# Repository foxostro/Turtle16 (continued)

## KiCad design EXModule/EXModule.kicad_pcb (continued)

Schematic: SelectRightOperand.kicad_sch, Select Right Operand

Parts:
C3, C4, C5, C6, C7: 100nF; C_0603_1608Metric_Pad1.08x0.95mm_HandSolder
U2, U3, U5, U6: 74AHCT16245; TSSOP-48_6.1x12.5mm_P0.5mm
U4: 74AHCT138; TSSOP-16_4.4x5mm_P0.65mm

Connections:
/EX Prototype Inputs/B0: U2.47 (1A1); also elsewhere on the board
/EX Prototype Inputs/B1: U2.46 (1A2); also elsewhere on the board
/EX Prototype Inputs/B2: U2.44 (1A3); also elsewhere on the board
/EX Prototype Inputs/B3: U2.43 (1A4); also elsewhere on the board
/EX Prototype Inputs/B4: U2.41 (1A5); also elsewhere on the board
/EX Prototype Inputs/B5: U2.40 (1A6); also elsewhere on the board
/EX Prototype Inputs/B6: U2.38 (1A7); also elsewhere on the board
/EX Prototype Inputs/B7: U2.37 (1A8); also elsewhere on the board
/EX Prototype Inputs/B8: U2.36 (2A1); also elsewhere on the board
/EX Prototype Inputs/B9: U2.35 (2A2); also elsewhere on the board
/EX Prototype Inputs/B10: U2.33 (2A3); also elsewhere on the board
/EX Prototype Inputs/B11: U2.32 (2A4); also elsewhere on the board
/EX Prototype Inputs/B12: U2.30 (2A5); also elsewhere on the board
/EX Prototype Inputs/B13: U2.29 (2A6); also elsewhere on the board
/EX Prototype Inputs/B14: U2.27 (2A7); also elsewhere on the board
/EX Prototype Inputs/B15: U2.26 (2A8); also elsewhere on the board
/EX Prototype Inputs/Ctl_EX3: U4.1 (A0); also elsewhere on the board
/EX Prototype Inputs/Ctl_EX4: U4.2 (A1); also elsewhere on the board
/EX Prototype Inputs/Ins_EX0: U3.47 (1A1), U5.47 (1A1), U6.47 (1A1); also elsewhere on the board
/EX Prototype Inputs/Ins_EX1: U3.46 (1A2), U5.46 (1A2), U6.46 (1A2); also elsewhere on the board
/EX Prototype Inputs/Ins_EX2: U3.44 (1A3), U6.44 (1A3); also elsewhere on the board
/EX Prototype Inputs/Ins_EX3: U3.43 (1A4), U6.43 (1A4); also elsewhere on the board
/EX Prototype Inputs/Ins_EX4: U3.26 (2A8), U3.27 (2A7), U3.29 (2A6), U3.30 (2A5), U3.32 (2A4), U3.33 (2A3), U3.35 (2A2), U3.36 (2A1), U3.37 (1A8), U3.38 (1A7), U3.40 (1A6), U3.41 (1A5), U6.41 (1A5); also elsewhere on the board
/EX Prototype Inputs/Ins_EX5: U6.40 (1A6); also elsewhere on the board
/EX Prototype Inputs/Ins_EX6: U6.38 (1A7); also elsewhere on the board
/EX Prototype Inputs/Ins_EX7: U6.37 (1A8); also elsewhere on the board
/EX Prototype Inputs/Ins_EX8: U5.44 (1A3), U6.36 (2A1); also elsewhere on the board
/EX Prototype Inputs/Ins_EX9: U5.43 (1A4), U6.35 (2A2); also elsewhere on the board
/EX Prototype Inputs/Ins_EX10: U5.26 (2A8), U5.27 (2A7), U5.29 (2A6), U5.30 (2A5), U5.32 (2A4), U5.33 (2A3), U5.35 (2A2), U5.36 (2A1), U5.37 (1A8), U5.38 (1A7), U5.40 (1A6), U5.41 (1A5), U6.26 (2A8), U6.27 (2A7), U6.29 (2A6), U6.30 (2A5), U6.32 (2A4), U6.33 (2A3); also elsewhere on the board
/EX/ALU/RightOp0: U2.2 (1B1), U3.2 (1B1), U5.2 (1B1), U6.2 (1B1); also elsewhere on the board
/EX/ALU/RightOp1: U2.3 (1B2), U3.3 (1B2), U5.3 (1B2), U6.3 (1B2); also elsewhere on the board
/EX/ALU/RightOp2: U2.5 (1B3), U3.5 (1B3), U5.5 (1B3), U6.5 (1B3); also elsewhere on the board
/EX/ALU/RightOp3: U2.6 (1B4), U3.6 (1B4), U5.6 (1B4), U6.6 (1B4); also elsewhere on the board
/EX/ALU/RightOp4: U2.8 (1B5), U3.8 (1B5), U5.8 (1B5), U6.8 (1B5); also elsewhere on the board
/EX/ALU/RightOp5: U2.9 (1B6), U3.9 (1B6), U5.9 (1B6), U6.9 (1B6); also elsewhere on the board
/EX/ALU/RightOp6: U2.11 (1B7), U3.11 (1B7), U5.11 (1B7), U6.11 (1B7); also elsewhere on the board
/EX/ALU/RightOp7: U2.12 (1B8), U3.12 (1B8), U5.12 (1B8), U6.12 (1B8); also elsewhere on the board
/EX/ALU/RightOp8: U2.13 (2B1), U3.13 (2B1), U5.13 (2B1), U6.13 (2B1); also elsewhere on the board
/EX/ALU/RightOp9: U2.14 (2B2), U3.14 (2B2), U5.14 (2B2), U6.14 (2B2); also elsewhere on the board
/EX/ALU/RightOp10: U2.16 (2B3), U3.16 (2B3), U5.16 (2B3), U6.16 (2B3); also elsewhere on the board
/EX/ALU/RightOp11: U2.17 (2B4), U3.17 (2B4), U5.17 (2B4), U6.17 (2B4); also elsewhere on the board
/EX/ALU/RightOp12: U2.19 (2B5), U3.19 (2B5), U5.19 (2B5), U6.19 (2B5); also elsewhere on the board
/EX/ALU/RightOp13: U2.20 (2B6), U3.20 (2B6), U5.20 (2B6), U6.20 (2B6); also elsewhere on the board
/EX/ALU/RightOp14: U2.22 (2B7), U3.22 (2B7), U5.22 (2B7), U6.22 (2B7); also elsewhere on the board
/EX/ALU/RightOp15: U2.23 (2B8), U3.23 (2B8), U5.23 (2B8), U6.23 (2B8); also elsewhere on the board
GND: C3.2, C4.2, C5.2, C6.2, C7.2, U2.4 (GND), U2.10 (GND), U2.15 (GND), U2.21 (GND), U2.28 (GND), U2.34 (GND), U2.39 (GND), U2.45 (GND), U3.4 (GND), U3.10 (GND), U3.15 (GND), U3.21 (GND), U3.28 (GND), U3.34 (GND), U3.39 (GND), U3.45 (GND), U4.3 (A2), U4.4 (E1), U4.5 (E2), U4.8 (GND), U5.4 (GND), U5.10 (GND), U5.15 (GND), U5.21 (GND), U5.28 (GND), U5.34 (GND), U5.39 (GND), U5.45 (GND), U6.4 (GND), U6.10 (GND), U6.15 (GND), U6.21 (GND), U6.28 (GND), U6.34 (GND), U6.39 (GND), U6.45 (GND); also elsewhere on the board
unnamed: U2.25 (2~OE), U2.48 (1~OE), U4.15 (O0)
unnamed: U3.25 (2~OE), U3.48 (1~OE), U4.14 (O1)
unnamed: U4.12 (O3), U6.25 (2~OE), U6.48 (1~OE)
unnamed: U4.13 (O2), U5.25 (2~OE), U5.48 (1~OE)
VCC: C3.1, C4.1, C5.1, C6.1, C7.1, U2.1 (1DIR), U2.7 (VCC), U2.18 (VCC), U2.24 (2DIR), U2.31 (VCC), U2.42 (VCC), U3.1 (1DIR), U3.7 (VCC), U3.18 (VCC), U3.24 (2DIR), U3.31 (VCC), U3.42 (VCC), U4.6 (E3), U4.16 (VCC), U5.1 (1DIR), U5.7 (VCC), U5.18 (VCC), U5.24 (2DIR), U5.31 (VCC), U5.42 (VCC), U6.1 (1DIR), U6.7 (VCC), U6.18 (VCC), U6.24 (2DIR), U6.31 (VCC), U6.42 (VCC); also elsewhere on the board

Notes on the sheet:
SelRightOp=0 —> Select Register B SelRightOp=1 —> Select Immediate ins[4:0] SelRightOp=2 —> Select Immediate ins[10:8, 1:0] SelRightOp=3 —> Select Immediate ins[10:0]

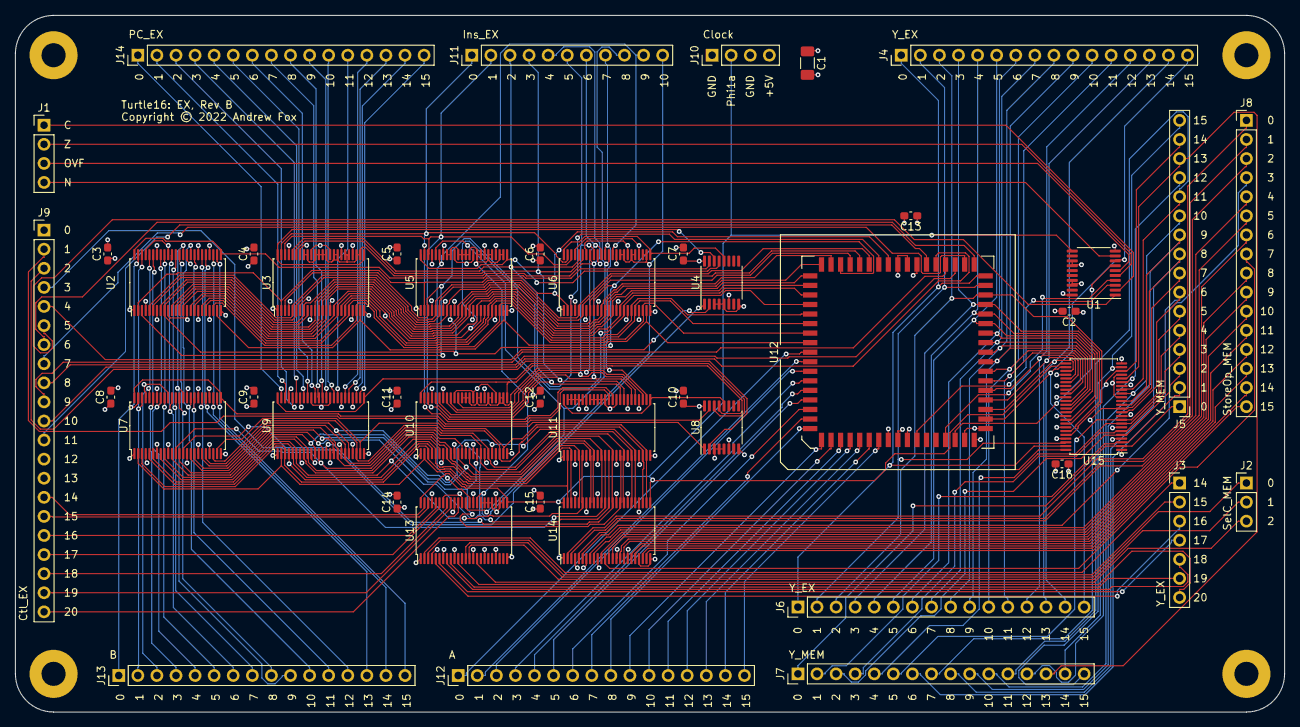
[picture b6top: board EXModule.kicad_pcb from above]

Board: 4 copper layers, 168.9 x 92.7 mm, 49 parts (0 on the bottom side), 185 nets.

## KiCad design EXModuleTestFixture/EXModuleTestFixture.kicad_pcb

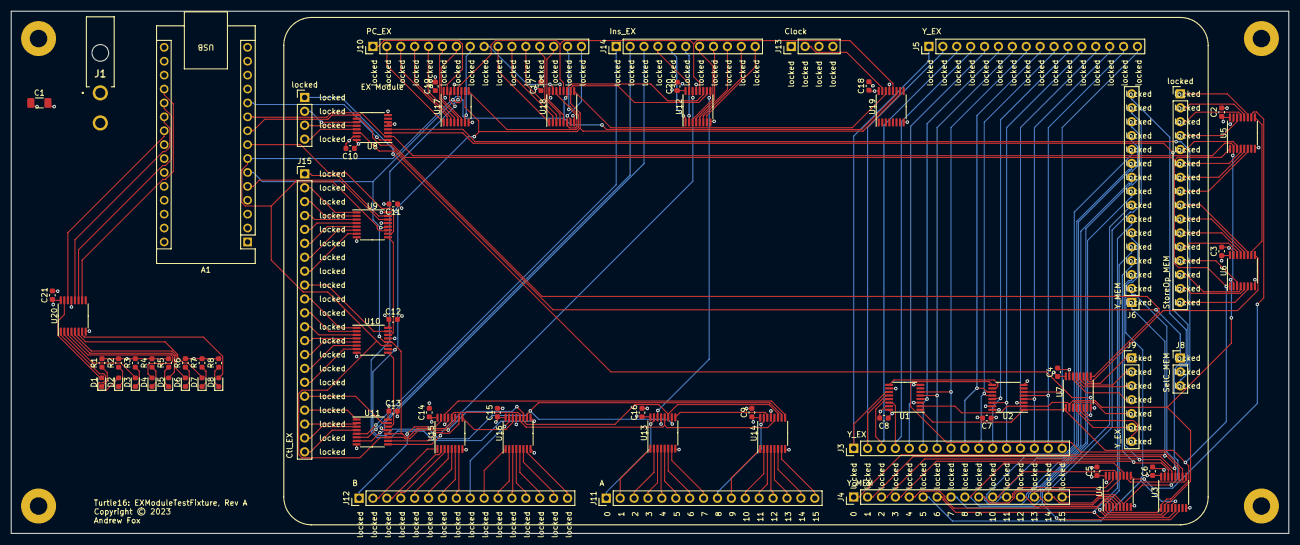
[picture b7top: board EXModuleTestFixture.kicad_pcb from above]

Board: 4 copper layers, 233.4 x 95.4 mm, 77 parts (0 on the bottom side), 189 nets.

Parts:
A1: Arduino_Nano_Every; Arduino_Nano
C1: 100µF; C_1206_3216Metric_Pad1.33x1.80mm_HandSolder
C2, C3, C4, C5, C6, C7, C8, C9, C10, C11, C12, C13, C14, C15, C16, C17, C18, C19, C20, C21: 0.1µF; C_0603_1608Metric
D1, D2, D3, D4, D5, D6, D7, D8: Red; LED_0603_1608Metric
H1, H2, H3, H4: MountingHole_Pad; MountingHole_3.2mm_M3_Pad
J1: Power; 172448-0002
J3, J5: Y_EX; PinHeader_1x16_P2.54mm_Vertical
J4, J6: Y_MEM; PinHeader_1x16_P2.54mm_Vertical
J8: SelC_MEM; PinHeader_1x03_P2.54mm_Vertical
J9: Y_EX; PinHeader_1x07_P2.54mm_Vertical
J10: PC_EX; PinHeader_1x16_P2.54mm_Vertical
J11: A; PinHeader_1x16_P2.54mm_Vertical
J12: B; PinHeader_1x16_P2.54mm_Vertical
J13: Clock; PinHeader_1x04_P2.54mm_Vertical
J14: Ins_EX; PinHeader_1x11_P2.54mm_Vertical
J15: Ctl_EX; PinHeader_1x21_P2.54mm_Vertical
R1, R2, R3, R4, R5, R6, R7, R8: 270R; C_0603_1608Metric
U1, U2, U3, U4, U5, U6, U7, U8: 74HC165; TSSOP-16_4.4x5mm_P0.65mm
U9, U10, U11, U12, U13, U14, U15, U16, U17, U18, U19, U20: 74HC595; TSSOP-16_4.4x5mm_P0.65mm
locked: StoreOp_MEM; PinHeader_1x16_P2.54mm_Vertical
locked#2: Flags; PinHeader_1x04_P2.54mm_Vertical

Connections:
/EX Prototype Inputs/A0: J11.1, U13.15 (QA)
/EX Prototype Inputs/A1: J11.2, U13.1 (QB)
/EX Prototype Inputs/A2: J11.3, U13.2 (QC)
/EX Prototype Inputs/A3: J11.4, U13.3 (QD)
/EX Prototype Inputs/A4: J11.5, U13.4 (QE)
/EX Prototype Inputs/A5: J11.6, U13.5 (QF)
/EX Prototype Inputs/A6: J11.7, U13.6 (QG)
/EX Prototype Inputs/A7: J11.8, U13.7 (QH)
/EX Prototype Inputs/A8: J11.9, U14.15 (QA)
/EX Prototype Inputs/A9: J11.10, U14.1 (QB)
/EX Prototype Inputs/A10: J11.11, U14.2 (QC)
/EX Prototype Inputs/A11: J11.12, U14.3 (QD)
/EX Prototype Inputs/A12: J11.13, U14.4 (QE)
/EX Prototype Inputs/A13: J11.14, U14.5 (QF)
/EX Prototype Inputs/A14: J11.15, U14.6 (QG)
/EX Prototype Inputs/A15: J11.16, U14.7 (QH)
/EX Prototype Inputs/B0: J12.1, U15.15 (QA)
/EX Prototype Inputs/B1: J12.2, U15.1 (QB)
/EX Prototype Inputs/B2: J12.3, U15.2 (QC)
/EX Prototype Inputs/B3: J12.4, U15.3 (QD)
/EX Prototype Inputs/B4: J12.5, U15.4 (QE)
/EX Prototype Inputs/B5: J12.6, U15.5 (QF)
/EX Prototype Inputs/B6: J12.7, U15.6 (QG)
/EX Prototype Inputs/B7: J12.8, U15.7 (QH)
/EX Prototype Inputs/B8: J12.9, U16.15 (QA)
/EX Prototype Inputs/B9: J12.10, U16.1 (QB)
/EX Prototype Inputs/B10: J12.11, U16.2 (QC)
/EX Prototype Inputs/B11: J12.12, U16.3 (QD)
/EX Prototype Inputs/B12: J12.13, U16.4 (QE)
/EX Prototype Inputs/B13: J12.14, U16.5 (QF)
/EX Prototype Inputs/B14: J12.15, U16.6 (QG)
/EX Prototype Inputs/B15: J12.16, U16.7 (QH)
/EX Prototype Inputs/Ctl_EX0: J15.1, U9.15 (QA)
/EX Prototype Inputs/Ctl_EX1: J15.2, U9.1 (QB)
/EX Prototype Inputs/Ctl_EX2: J15.3, U9.2 (QC)
/EX Prototype Inputs/Ctl_EX3: J15.4, U9.3 (QD)
/EX Prototype Inputs/Ctl_EX4: J15.5, U9.4 (QE)
/EX Prototype Inputs/Ctl_EX5: J15.6, U9.5 (QF)
/EX Prototype Inputs/Ctl_EX6: J15.7, U9.6 (QG)
/EX Prototype Inputs/Ctl_EX7: J15.8, U9.7 (QH)
/EX Prototype Inputs/Ctl_EX8: J15.9, U10.15 (QA)
/EX Prototype Inputs/Ctl_EX9: J15.10, U10.1 (QB)
/EX Prototype Inputs/Ctl_EX10: J15.11, U10.2 (QC)
/EX Prototype Inputs/Ctl_EX11: J15.12, U10.3 (QD)
/EX Prototype Inputs/Ctl_EX12: J15.13, U10.4 (QE)
/EX Prototype Inputs/Ctl_EX13: J15.14, U10.5 (QF)
/EX Prototype Inputs/Ctl_EX14: J15.15, U10.6 (QG)
/EX Prototype Inputs/Ctl_EX15: J15.16, U10.7 (QH)
/EX Prototype Inputs/Ctl_EX16: J15.17, U11.15 (QA)
/EX Prototype Inputs/Ctl_EX17: J15.18, U11.1 (QB)
/EX Prototype Inputs/Ctl_EX18: J15.19, U11.2 (QC)
/EX Prototype Inputs/Ctl_EX19: J15.20, U11.3 (QD)
/EX Prototype Inputs/Ctl_EX20: J15.21, U11.4 (QE)
/EX Prototype Inputs/Ins_EX0: J14.1, U11.5 (QF)
/EX Prototype Inputs/Ins_EX1: J14.2, U11.6 (QG)
/EX Prototype Inputs/Ins_EX2: J14.3, U11.7 (QH)
/EX Prototype Inputs/Ins_EX3: J14.4, U12.15 (QA)
/EX Prototype Inputs/Ins_EX4: J14.5, U12.1 (QB)
/EX Prototype Inputs/Ins_EX5: J14.6, U12.2 (QC)
/EX Prototype Inputs/Ins_EX6: J14.7, U12.3 (QD)
/EX Prototype Inputs/Ins_EX7: J14.8, U12.4 (QE)
/EX Prototype Inputs/Ins_EX8: J14.9, U12.5 (QF)
/EX Prototype Inputs/Ins_EX9: J14.10, U12.6 (QG)
/EX Prototype Inputs/Ins_EX10: J14.11, U12.7 (QH)
/EX Prototype Inputs/PC_EX0: J10.1, U17.15 (QA)
/EX Prototype Inputs/PC_EX1: J10.2, U17.1 (QB)
/EX Prototype Inputs/PC_EX2: J10.3, U17.2 (QC)
/EX Prototype Inputs/PC_EX3: J10.4, U17.3 (QD)
/EX Prototype Inputs/PC_EX4: J10.5, U17.4 (QE)
/EX Prototype Inputs/PC_EX5: J10.6, U17.5 (QF)
/EX Prototype Inputs/PC_EX6: J10.7, U17.6 (QG)
/EX Prototype Inputs/PC_EX7: J10.8, U17.7 (QH)
/EX Prototype Inputs/PC_EX8: J10.9, U18.15 (QA)
/EX Prototype Inputs/PC_EX9: J10.10, U18.1 (QB)
/EX Prototype Inputs/PC_EX10: J10.11, U18.2 (QC)
/EX Prototype Inputs/PC_EX11: J10.12, U18.3 (QD)
/EX Prototype Inputs/PC_EX12: J10.13, U18.4 (QE)
/EX Prototype Inputs/PC_EX13: J10.14, U18.5 (QF)
/EX Prototype Inputs/PC_EX14: J10.15, U18.6 (QG)
/EX Prototype Inputs/PC_EX15: J10.16, U18.7 (QH)
/EX Prototype Inputs/Phi1a: J13.2, U19.15 (QA)
/EX Prototype Outputs/Carry: U7.6 (D7), locked#2.1
/EX Prototype Outputs/Ctl_MEM14: J9.1, U7.11 (D0)
/EX Prototype Outputs/Ctl_MEM15: J9.2, U7.12 (D1)
/EX Prototype Outputs/Ctl_MEM16: J9.3, U7.13 (D2)
/EX Prototype Outputs/Ctl_MEM17: J9.4, U7.14 (D3)
/EX Prototype Outputs/Ctl_MEM18: J9.5, U7.3 (D4)
/EX Prototype Outputs/Ctl_MEM19: J9.6, U7.4 (D5)
/EX Prototype Outputs/Ctl_MEM20: J9.7, U7.5 (D6)
/EX Prototype Outputs/N: U8.13 (D2), locked#2.4
/EX Prototype Outputs/OVF: U8.12 (D1), locked#2.3
/EX Prototype Outputs/SelC_MEM0: J8.1, U8.14 (D3)
/EX Prototype Outputs/SelC_MEM1: J8.2, U8.3 (D4)
/EX Prototype Outputs/SelC_MEM2: J8.3, U8.4 (D5)
/EX Prototype Outputs/StoreOp_MEM0: U5.11 (D0), locked.1
/EX Prototype Outputs/StoreOp_MEM1: U5.12 (D1), locked.2
/EX Prototype Outputs/StoreOp_MEM2: U5.13 (D2), locked.3
/EX Prototype Outputs/StoreOp_MEM3: U5.14 (D3), locked.4
/EX Prototype Outputs/StoreOp_MEM4: U5.3 (D4), locked.5
/EX Prototype Outputs/StoreOp_MEM5: U5.4 (D5), locked.6
/EX Prototype Outputs/StoreOp_MEM6: U5.5 (D6), locked.7
/EX Prototype Outputs/StoreOp_MEM7: U5.6 (D7), locked.8
/EX Prototype Outputs/StoreOp_MEM8: U6.11 (D0), locked.9
/EX Prototype Outputs/StoreOp_MEM9: U6.12 (D1), locked.10
/EX Prototype Outputs/StoreOp_MEM10: U6.13 (D2), locked.11
/EX Prototype Outputs/StoreOp_MEM11: U6.14 (D3), locked.12
/EX Prototype Outputs/StoreOp_MEM12: U6.3 (D4), locked.13
/EX Prototype Outputs/StoreOp_MEM13: U6.4 (D5), locked.14
/EX Prototype Outputs/StoreOp_MEM14: U6.5 (D6), locked.15
/EX Prototype Outputs/StoreOp_MEM15: U6.6 (D7), locked.16
/EX Prototype Outputs/Y_EX0: J3.1, J5.1, U1.11 (D0)
/EX Prototype Outputs/Y_EX1: J3.2, J5.2, U1.12 (D1)
/EX Prototype Outputs/Y_EX2: J3.3, J5.3, U1.13 (D2)
/EX Prototype Outputs/Y_EX3: J3.4, J5.4, U1.14 (D3)
/EX Prototype Outputs/Y_EX4: J3.5, J5.5, U1.3 (D4)
/EX Prototype Outputs/Y_EX5: J3.6, J5.6, U1.4 (D5)
/EX Prototype Outputs/Y_EX6: J3.7, J5.7, U1.5 (D6)
/EX Prototype Outputs/Y_EX7: J3.8, J5.8, U1.6 (D7)
/EX Prototype Outputs/Y_EX8: J3.9, J5.9, U2.11 (D0)
/EX Prototype Outputs/Y_EX9: J3.10, J5.10, U2.12 (D1)
/EX Prototype Outputs/Y_EX10: J3.11, J5.11, U2.13 (D2)
/EX Prototype Outputs/Y_EX11: J3.12, J5.12, U2.14 (D3)
/EX Prototype Outputs/Y_EX12: J3.13, J5.13, U2.3 (D4)
/EX Prototype Outputs/Y_EX13: J3.14, J5.14, U2.4 (D5)
/EX Prototype Outputs/Y_EX14: J3.15, J5.15, U2.5 (D6)
/EX Prototype Outputs/Y_EX15: J3.16, J5.16, U2.6 (D7)
/EX Prototype Outputs/Y_MEM0: J4.1, J6.1, U3.11 (D0)
/EX Prototype Outputs/Y_MEM1: J4.2, J6.2, U3.12 (D1)
/EX Prototype Outputs/Y_MEM2: J4.3, J6.3, U3.13 (D2)
/EX Prototype Outputs/Y_MEM3: J4.4, J6.4, U3.14 (D3)
/EX Prototype Outputs/Y_MEM4: J4.5, J6.5, U3.3 (D4)
/EX Prototype Outputs/Y_MEM5: J4.6, J6.6, U3.4 (D5)
/EX Prototype Outputs/Y_MEM6: J4.7, J6.7, U3.5 (D6)
/EX Prototype Outputs/Y_MEM7: J4.8, J6.8, U3.6 (D7)
/EX Prototype Outputs/Y_MEM8: J4.9, J6.9, U4.11 (D0)
/EX Prototype Outputs/Y_MEM9: J4.10, J6.10, U4.12 (D1)
/EX Prototype Outputs/Y_MEM10: J4.11, J6.11, U4.13 (D2)
/EX Prototype Outputs/Y_MEM11: J4.12, J6.12, U4.14 (D3)
/EX Prototype Outputs/Y_MEM12: J4.13, J6.13, U4.3 (D4)
/EX Prototype Outputs/Y_MEM13: J4.14, J6.14, U4.4 (D5)
/EX Prototype Outputs/Y_MEM14: J4.15, J6.15, U4.5 (D6)
/EX Prototype Outputs/Y_MEM15: J4.16, J6.16, U4.6 (D7)
/EX Prototype Outputs/Z: U8.11 (D0), locked#2.2
/LED Output/RCLK: A1.21 (A2), U20.12 (RCLK)
/LED Output/SCK: A1.20 (A1), U20.11 (SRCLK)
/LED Output/SI: A1.22 (A3), U20.14 (SER)
/LED Output/~CLR: A1.19 (A0), U20.10 (~SRCLR)
/Test Fixture Inputs/SCK: A1.10 (D7), U1.2 (CP), U2.2 (CP), U3.2 (CP), U4.2 (CP), U5.2 (CP), U6.2 (CP), U7.2 (CP), U8.2 (CP)
/Test Fixture Inputs/SO: A1.9 (D6), U8.9 (Q7)
/Test Fixture Inputs/~PL: A1.11 (D8), U1.1 (~PL), U2.1 (~PL), U3.1 (~PL), U4.1 (~PL), U5.1 (~PL), U6.1 (~PL), U7.1 (~PL), U8.1 (~PL)
/Test Fixture Outputs/RCLK: A1.6 (D3), U9.12 (RCLK), U10.12 (RCLK), U11.12 (RCLK), U12.12 (RCLK), U13.12 (RCLK), U14.12 (RCLK), U15.12 (RCLK), U16.12 (RCLK), U17.12 (RCLK), U18.12 (RCLK), U19.12 (RCLK)
/Test Fixture Outputs/SCK: A1.7 (D4), U9.11 (SRCLK), U10.11 (SRCLK), U11.11 (SRCLK), U12.11 (SRCLK), U13.11 (SRCLK), U14.11 (SRCLK), U15.11 (SRCLK), U16.11 (SRCLK), U17.11 (SRCLK), U18.11 (SRCLK), U19.11 (SRCLK)
/Test Fixture Outputs/SI: A1.5 (D2), U9.14 (SER)
/Test Fixture Outputs/~CLR: A1.8 (D5), U9.10 (~SRCLR), U10.10 (~SRCLR), U11.10 (~SRCLR), U12.10 (~SRCLR), U13.10 (~SRCLR), U14.10 (~SRCLR), U15.10 (~SRCLR), U16.10 (~SRCLR), U17.10 (~SRCLR), U18.10 (~SRCLR), U19.10 (~SRCLR)
GND: A1.4 (GND), A1.29 (GND), C1.2, C2.2, C3.2, C4.2, C5.2, C6.2, C7.2, C8.2, C9.2, C10.2, C11.2, C12.2, C13.2, C14.2, C15.2, C16.2, C17.2, C18.2, C19.2, C20.2, C21.2, H1.1, H2.1, H3.1, H4.1, J1.2, J13.1, J13.3, R1.2, R2.2, R3.2, R4.2, R5.2, R6.2, R7.2, R8.2, U1.8 (GND), U1.10 (DS), U1.15 (~CE), U2.8 (GND), U2.15 (~CE), U3.8 (GND), U3.15 (~CE), U4.8 (GND), U4.15 (~CE), U5.8 (GND), U5.15 (~CE), U6.8 (GND), U6.15 (~CE), U7.8 (GND), U7.15 (~CE), U8.5 (D6), U8.6 (D7), U8.8 (GND), U8.15 (~CE), U9.8 (GND), U9.13 (~OE), U10.8 (GND), U10.13 (~OE), U11.8 (GND), U11.13 (~OE), U12.8 (GND), U12.13 (~OE), U13.8 (GND), U13.13 (~OE), U14.8 (GND), U14.13 (~OE), U15.8 (GND), U15.13 (~OE), U16.8 (GND), U16.13 (~OE), U17.8 (GND), U17.13 (~OE), U18.8 (GND), U18.13 (~OE), U19.8 (GND), U19.13 (~OE), U20.8 (GND), U20.13 (~OE)
unnamed: D1.2 (A), U20.15 (QA)
unnamed: D1.1 (K), R1.1
unnamed: D2.2 (A), U20.1 (QB)
unnamed: D2.1 (K), R2.1
unnamed: D3.2 (A), U20.2 (QC)
unnamed: D3.1 (K), R3.1
unnamed: D4.2 (A), U20.3 (QD)
unnamed: D4.1 (K), R4.1
unnamed: D5.2 (A), U20.4 (QE)
unnamed: D5.1 (K), R5.1
unnamed: D6.2 (A), U20.5 (QF)
unnamed: D6.1 (K), R6.1
unnamed: D7.2 (A), U20.6 (QG)
unnamed: D7.1 (K), R7.1
unnamed: D8.2 (A), U20.7 (QH)
unnamed: D8.1 (K), R8.1
unnamed: U1.9 (Q7), U2.10 (DS)
unnamed: U2.9 (Q7), U3.10 (DS)
unnamed: U3.9 (Q7), U4.10 (DS)
unnamed: U4.9 (Q7), U5.10 (DS)
unnamed: U5.9 (Q7), U6.10 (DS)
unnamed: U6.9 (Q7), U7.10 (DS)
unnamed: U7.9 (Q7), U8.10 (DS)
unnamed: U10.9 (QH'), U11.14 (SER)
unnamed: U9.9 (QH'), U10.14 (SER)
unnamed: U11.9 (QH'), U12.14 (SER)
unnamed: U12.9 (QH'), U13.14 (SER)
unnamed: U13.9 (QH'), U14.14 (SER)
unnamed: U14.9 (QH'), U15.14 (SER)
unnamed: U15.9 (QH'), U16.14 (SER)
unnamed: U16.9 (QH'), U17.14 (SER)
unnamed: U17.9 (QH'), U18.14 (SER)
unnamed: U18.9 (QH'), U19.14 (SER)
VCC: A1.3 (~RESET), A1.28 (~RESET), A1.30 (VIN), C1.1, C2.1, C3.1, C4.1, C5.1, C6.1, C7.1, C8.1, C9.1, C10.1, C11.1, C12.1, C13.1, C14.1, C15.1, C16.1, C17.1, C18.1, C19.1, C20.1, C21.1, J1.1, J13.4, U1.16 (VCC), U2.16 (VCC), U3.16 (VCC), U4.16 (VCC), U5.16 (VCC), U6.16 (VCC), U7.16 (VCC), U8.16 (VCC), U9.16 (VCC), U10.16 (VCC), U11.16 (VCC), U12.16 (VCC), U13.16 (VCC), U14.16 (VCC), U15.16 (VCC), U16.16 (VCC), U17.16 (VCC), U18.16 (VCC), U19.16 (VCC), U20.16 (VCC)
